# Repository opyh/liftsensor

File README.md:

# liftsensor

Measures acceleration to find out if an elevator works and updates its status on [accessibility.cloud](https://www.accessibility.cloud).

## Design / photos

This is how the sensor looks:

## Technical specification

- Plug & Play installation using the maintenance 230V AC connector on top of the elevator's cabin
- Typical power consumption <1W, micro USB power adapter
- Sets the elevator's status to 'unknown' on [accessibility.cloud](https://www.accessibility.cloud) if it has not been in use within typical usage time intervals
- M2M Nano SIM card leverages a comprehensive network of carriers to provide service in over 100 countries out of the box
- Built-in 150mA battery to actively send a maintenance event in case the device is actively unplugged
- Open source design based on [Particle Electron](https://docs.particle.io/datasheets/electron-(cellular)/electron-datasheet/) IoT platform
- Analog Devices ADXL335 3-Axis ±3 g acceleration sensor
- U-blox SARA-U260/U270 3G module for communication with [accessibility.cloud](https://www.accessibility.cloud)
- STM32F205RGT6 120MHz ARM Cortex M3 microcontroller
- 1MB flash, 128KB RAM
- Allows firmware updates over-the-air
- RGB status LED
- Real-time operation system (RTOS)

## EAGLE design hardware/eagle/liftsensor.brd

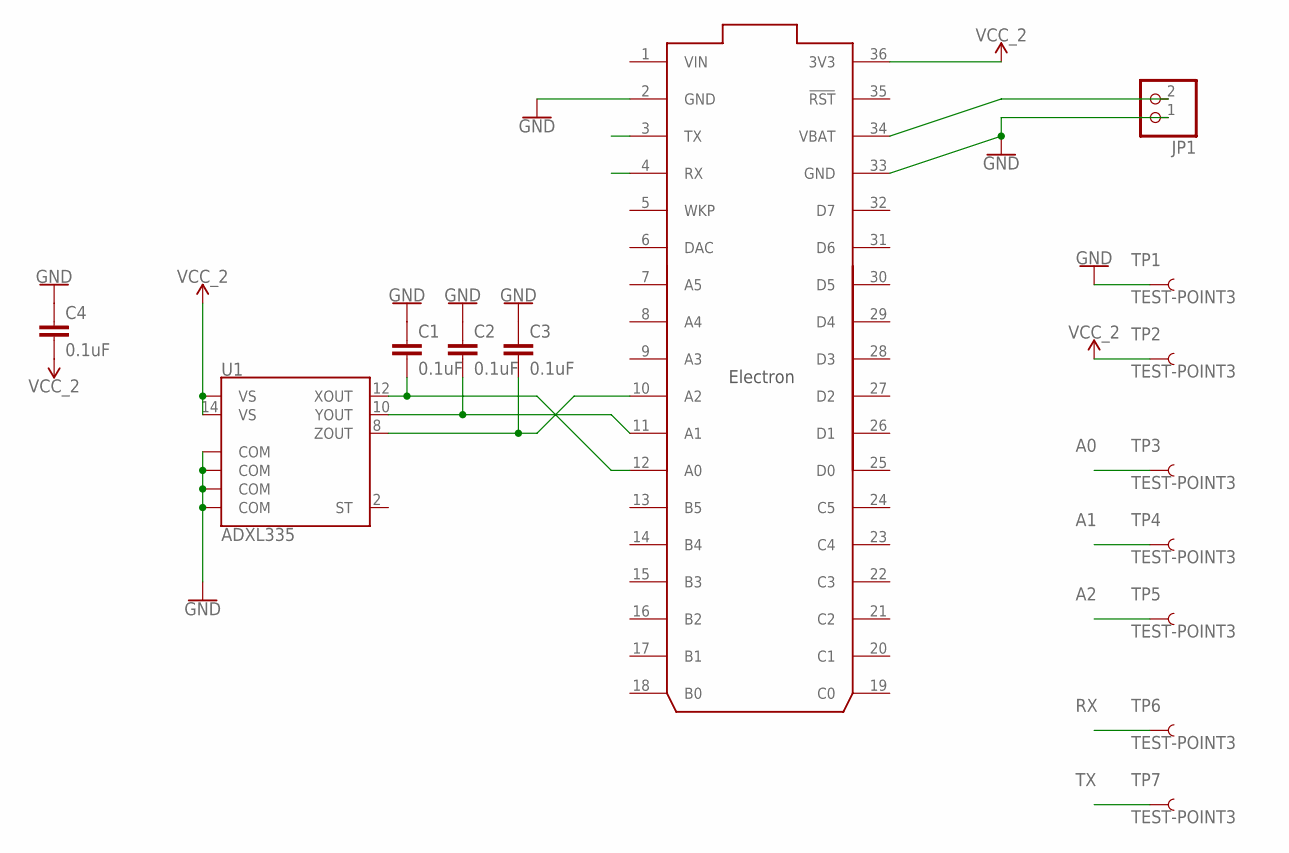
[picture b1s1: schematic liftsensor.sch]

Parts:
C1, C2, C3, C4: 0.1uF; 0603
EL: ELECTRON_WITH_HEADERS; ELECTRON
JP1: PINHD-1X2/90; 1X02/90
TP1, TP2, TP3, TP4, TP5, TP6, TP7: TEST-POINT3; PAD.03X.03
U1: ADXL335; LFCSP-16-4X4

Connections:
A0: C1.2, EL.12 (A0), TP3.P$1, U1.12 (XOUT)
A1: C2.2, EL.11 (A1), TP4.P$1, U1.10 (YOUT)
A2: C3.2, EL.10 (A2), TP5.P$1, U1.8 (ZOUT)
GND: C1.1, C2.1, C3.1, C4.1, EL.2 (GND), EL.33 (GND), JP1.1, TP1.P$1, U1.3 (COM), U1.5 (COM), U1.6 (COM), U1.7 (COM)
RX: EL.4 (RX), TP6.P$1
TX: EL.3 (TX), TP7.P$1
VBAT: EL.34 (VBAT), JP1.2
VCC_2: C4.2, EL.36 (3V3), TP2.P$1, U1.14 (VS), U1.15 (VS)
VIN: EL.1 (VIN)

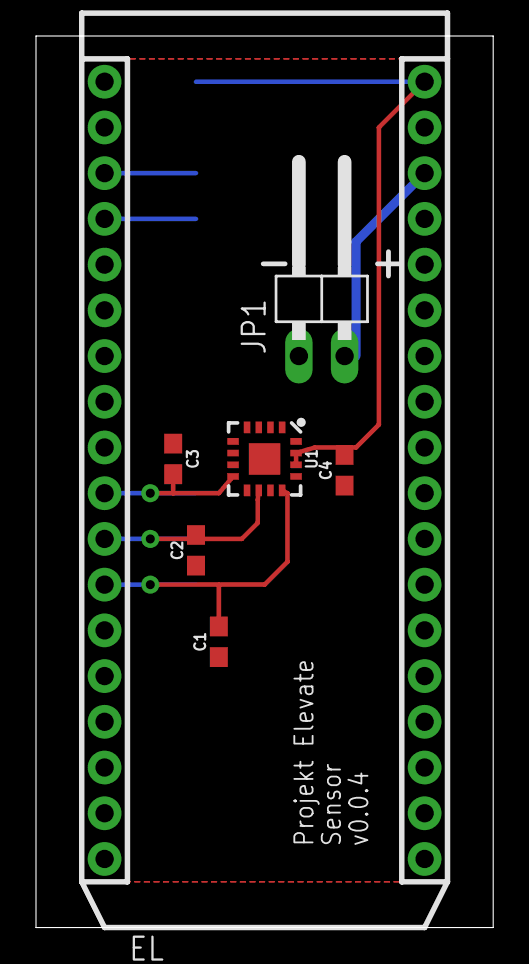
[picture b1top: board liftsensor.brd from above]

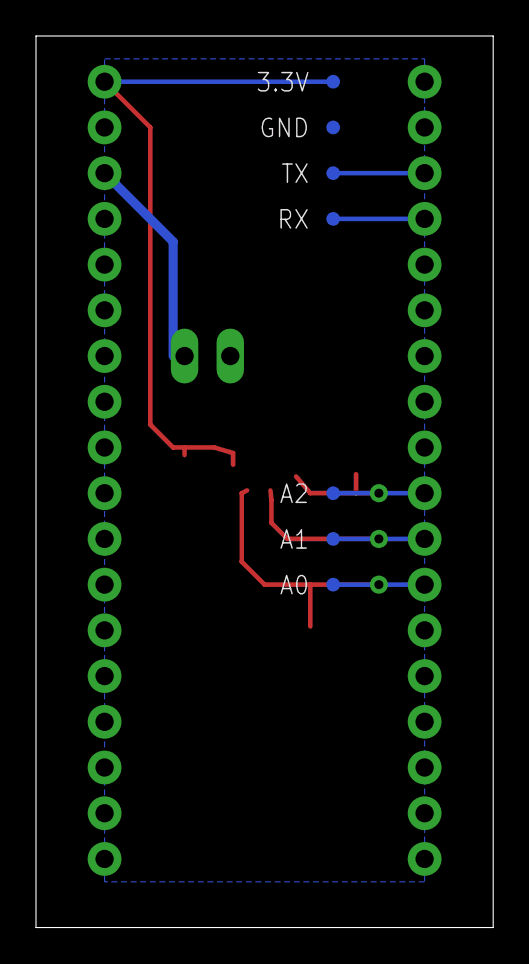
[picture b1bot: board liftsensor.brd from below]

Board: 2 copper layers, 25.4 x 49.5 mm, 14 parts (7 on the bottom side), 8 nets.

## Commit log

2017-04-21 Rename wakeUpOnD0.ino to PhotonADXLWakeUpOnD0.ino
2017-04-21 Add Fritzing schema for ADXL / Particle liftsensor
2017-12-28 Add eagle files of first ordered board
2017-12-28 Order files in folders
2017-12-28 Add first order BOM and gerber files
2017-12-28 Fix bug in no-acceleration timeout handling
2017-12-28 Add README.md + LICENSE
2017-12-28 Add VSCode settings files
2017-12-28 Remove `\r` from wake-up example code
2018-02-05 Update Eagle designs
2018-02-05 Add documentation
2018-03-28 Update hardware design with fixes, add ordered gerber files
2018-03-28 Improve local firmware development process
    - Use VSCode with `po` instead of Particle Dev
    - Faster local firmware flashing
    - local builds without Particle cloud
    - Split code parts into modules
    - Add dev setup documentation
2018-04-03 Improve code + measurement stability
    Make diagnostics easier:
    - Refactor code to use state machines
    - Send cell location + cell tower infos on device start
    - Filter measurements with a DC bias filter
    - Allow to use all axes for measurement in case of a faulty installation
    - Better measurement debouncing (fixed time window) and exponential backoff for inactivity events
2018-04-04 Cleanup, add more diagnostics code, more stable measurement
    - Remove obsolete functions/variables
    - Calculate speed from acceleration – speed thresholds catch elevator stopping/starting movements much better than accelerations and are more robust against noise like entering/existing passengers or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
    - Queue events when there is no connection
    - Add more remote debugging code for diagnostics
    -
2020-01-08 initial setup on ubuntu and vscode
2020-03-10 ubirch modification for linux usage
2020-07-30 Store settings in EEPROM + Battery handling
2020-07-30 Improve configured hard-coded values
2020-07-30 Use correct DC-filtered speed value
2020-07-30 Add missing rootController.init() call
2020-07-30 Add product ID/version macros
2020-07-30 Add 3D print STL files
2020-07-30 Update top logos DXF

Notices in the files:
parts and their libraries:
SparkFun-Capacitors: Licensing: Creative Commons ShareAlike 4.0 International - https://creativecommons.org/licenses/by-sa/4.0
Particle-Devices: Licensing: Designed by Particle.
